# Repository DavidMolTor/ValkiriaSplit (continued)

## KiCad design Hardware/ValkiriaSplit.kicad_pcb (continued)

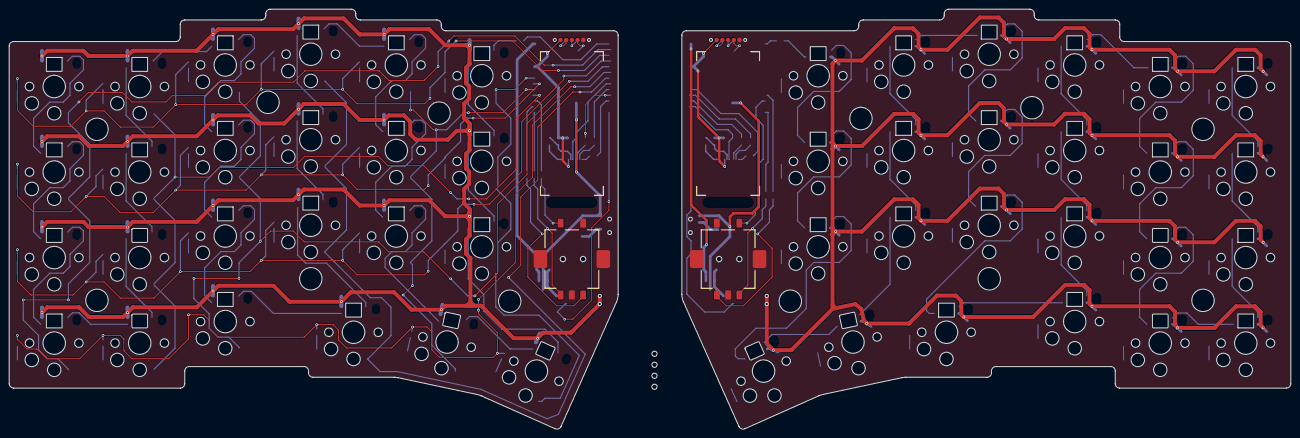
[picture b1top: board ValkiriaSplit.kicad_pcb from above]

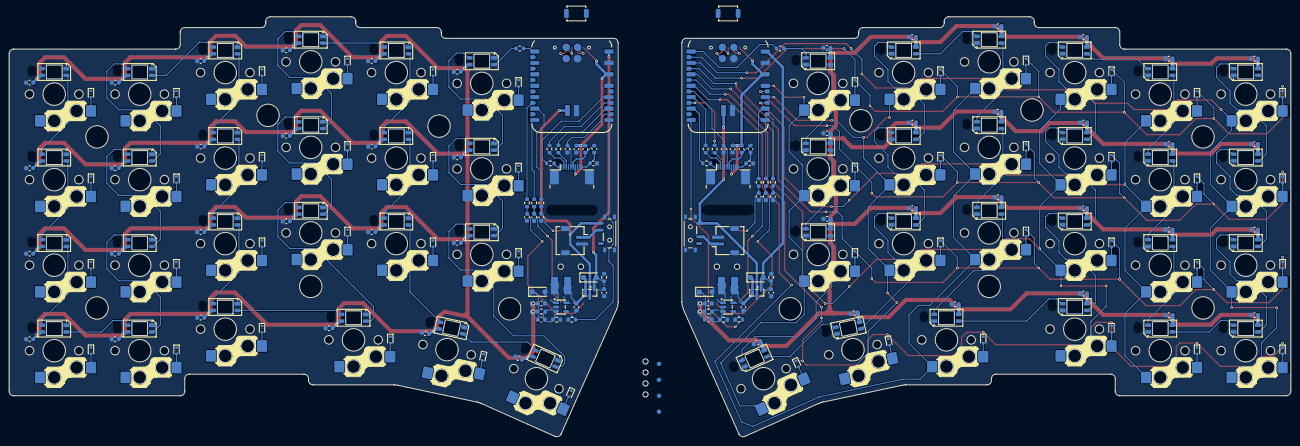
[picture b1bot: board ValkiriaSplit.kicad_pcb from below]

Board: 2 copper layers, 285.5 x 93.5 mm, 270 parts (214 on the bottom side), 173 nets.
